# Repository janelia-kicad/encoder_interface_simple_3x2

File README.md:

- [Repository Information](#orgb147bf3)
  - [Description](#org8e3bae9)
- [Images](#org7099fdc)
- [Schematic](#org4a67db8)
- [Gerbers](#org8729698)
- [Bill of Materials](#org40f1ed6)
  - [PCB Parts](#org051be0c)
  - [Supplemental Parts](#orgbf1fa54)
  - [Vendor Parts Lists](#org75a438f)
- [Supplemental Documentation](#org5ec4243)
  - [Assembly Instructions](#org6c46454)
- [Manufacturing Archive](#org6b4d140)

# Repository Information

-   **Name:** encoder\_interface\_simple\_3x2
-   **Version:** 1.1
-   **License:** Open-Source Hardware
-   **URL:** <https://github.com/janelia-kicad/encoder_interface_simple_3x2>
-   **Author:** Peter Polidoro
-   **Email:** peter@polidoro.io

## Description

This board provides a simple encoder interace with buffered encoder signal outputs.

# Images

# Schematic

[./schematic/encoder\_interface\_simple\_3x2.pdf](./schematic/encoder_interface_simple_3x2.pdf)

# Gerbers

# Bill of Materials

## PCB Parts

| Item | Reference(s) | Quantity | Manufacturer                    | Manufacturer Part Number | Vendor   | Vendor Part Number | Description                                                       | Package            |
|---- |------------ |-------- |------------------------------- |------------------------ |-------- |------------------ |----------------------------------------------------------------- |------------------ |
| 1    | C1           | 1        | KEMET                           | C1210X104K1RAC7800       | Digi-Key | 399-13229-1-ND     | CAP CER 0.1UF 50V 10% X7R                                         | 1210 (3225 Metric) |
| 2    | MDB1         | 2        | Sullins Connector Solutions     | PBC16SAAN                | Digi-Key | S1011E-16-ND       | 16 Position Header Through Hole Male Pins                         |                    |
| 3    | P1           | 1        | Amphenol RF                     | 112661                   | Digi-Key | ACX1655-ND         | CONN BNC JACK R/A 75 OHM PCB                                      |                    |
| 4    | P2           | 1        | Molex                           | 0740991005               | Digi-Key | WM7205-ND          | CONN HEADER .100 VERT 5POS SMD                                    |                    |
| 5    | R1 R2        | 2        | Panasonic Electronic Components | ERJ-14NF3161U            | Digi-Key | P3.16KAACT-ND      | RES SMD 3.16K OHM 1% 1/2W 1210                                    |                    |
| 6    | U1           | 1        | Texas Instruments               | SN74ABT541BDWR           | Digi-Key | 296-14668-1-ND     | Buffer Non-Inverting 1 Element 8 Bit per Element Push-Pull Output | 20-SOIC            |

## Supplemental Parts

| Item | Quantity | Manufacturer            | Manufacturer Part Number | Vendor   | Vendor Part Number | Description                      |
|---- |-------- |----------------------- |------------------------ |-------- |------------------ |-------------------------------- |
| 1    | 1        | Molex                   | 0050579405               | Digi-Key | WM2903-ND          | CONN HOUSING 5POS .100 W/LATCH   |
| 2    | 5        | Molex                   | 0016021117               | Digi-Key | WM2572-ND          | CONN SOCKET 24-30AWG CRIMP GOLD  |
| 3    | 2        | TPI (Test Products Int) | 58-024-1M                | Digi-Key | 290-1010-ND        | CBL ASSY BNC PLUG-PLUG RG58 24IN |

## Vendor Parts Lists

[./bom/Digi-Key\_parts.csv](./bom/Digi-Key_parts.csv)

[./bom/supplemental\_Digi-Key\_parts.csv](./bom/supplemental_Digi-Key_parts.csv)

# Supplemental Documentation

## Assembly Instructions

-   Solder surface mount and through hole components onto the pcb.

# Manufacturing Archive

Send manufacturing zip file to your favorite PCB manufacturer for fabrication.

[./manufacturing/encoder\_interface\_simple\_3x2\_v1.1.zip](./manufacturing/encoder_interface_simple_3x2_v1.1.zip)

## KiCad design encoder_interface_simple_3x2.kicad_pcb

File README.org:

# Created 2020-10-30 Fri 10:11
#+OPTIONS: title:nil author:nil email:nil toc:t |:t ^:nil
* Repository Information

- Name :: encoder_interface_simple_3x2
- Version :: 1.1
- License :: Open-Source Hardware
- URL :: https://github.com/janelia-kicad/encoder_interface_simple_3x2
- Author :: Peter Polidoro
- Email :: peter@polidoro.io

** Description

This board provides a simple encoder interace with buffered encoder signal
outputs.

* Images

* Schematic

[[file:./schematic/encoder_interface_simple_3x2.pdf][./schematic/encoder_interface_simple_3x2.pdf]]

[[file:./schematic/images/schematic00.png]]

[[file:./schematic/images/schematic01.png]]

* Gerbers

[[file:./gerbers/images/gerbers00.png]]

[[file:./gerbers/images/gerbers01.png]]

* Bill of Materials

** PCB Parts

| Item | Reference(s) | Quantity | Manufacturer                    | Manufacturer Part Number | Vendor   | Vendor Part Number | Description                                                       | Package            |
|------+--------------+----------+---------------------------------+--------------------------+----------+--------------------+-------------------------------------------------------------------+--------------------|
|    1 | C1           |        1 | KEMET                           | C1210X104K1RAC7800       | Digi-Key | 399-13229-1-ND     | CAP CER 0.1UF 50V 10% X7R                                         | 1210 (3225 Metric) |
|    2 | MDB1         |        2 | Sullins Connector Solutions     | PBC16SAAN                | Digi-Key | S1011E-16-ND       | 16 Position Header Through Hole Male Pins                         |                    |
|    3 | P1           |        1 | Amphenol RF                     | 112661                   | Digi-Key | ACX1655-ND         | CONN BNC JACK R/A 75 OHM PCB                                      |                    |
|    4 | P2           |        1 | Molex                           | 0740991005               | Digi-Key | WM7205-ND          | CONN HEADER .100 VERT 5POS SMD                                    |                    |
|    5 | R1 R2        |        2 | Panasonic Electronic Components | ERJ-14NF3161U            | Digi-Key | P3.16KAACT-ND      | RES SMD 3.16K OHM 1% 1/2W 1210                                    |                    |
|    6 | U1           |        1 | Texas Instruments               | SN74ABT541BDWR           | Digi-Key | 296-14668-1-ND     | Buffer Non-Inverting 1 Element 8 Bit per Element Push-Pull Output | 20-SOIC            |

** Supplemental Parts

| Item | Quantity | Manufacturer            | Manufacturer Part Number | Vendor   | Vendor Part Number | Description                      |
|------+----------+-------------------------+--------------------------+----------+--------------------+----------------------------------|
|    1 |        1 | Molex                   |               0050579405 | Digi-Key | WM2903-ND          | CONN HOUSING 5POS .100 W/LATCH   |
|    2 |        5 | Molex                   |               0016021117 | Digi-Key | WM2572-ND          | CONN SOCKET 24-30AWG CRIMP GOLD  |
|    3 |        2 | TPI (Test Products Int) |                58-024-1M | Digi-Key | 290-1010-ND        | CBL ASSY BNC PLUG-PLUG RG58 24IN |
#+TBLFM: $1=@#-1

** Vendor Parts Lists

[[file:./bom/Digi-Key_parts.csv][./bom/Digi-Key_parts.csv]]

[[file:./bom/supplemental_Digi-Key_parts.csv][./bom/supplemental_Digi-Key_parts.csv]]

* Supplemental Documentation

** Assembly Instructions

- Solder surface mount and through hole components onto the pcb.

* Manufacturing Archive

Send manufacturing zip file to your favorite PCB manufacturer for fabrication.

[[file:./manufacturing/encoder_interface_simple_3x2_v1.1.zip][./manufacturing/encoder_interface_simple_3x2_v1.1.zip]]

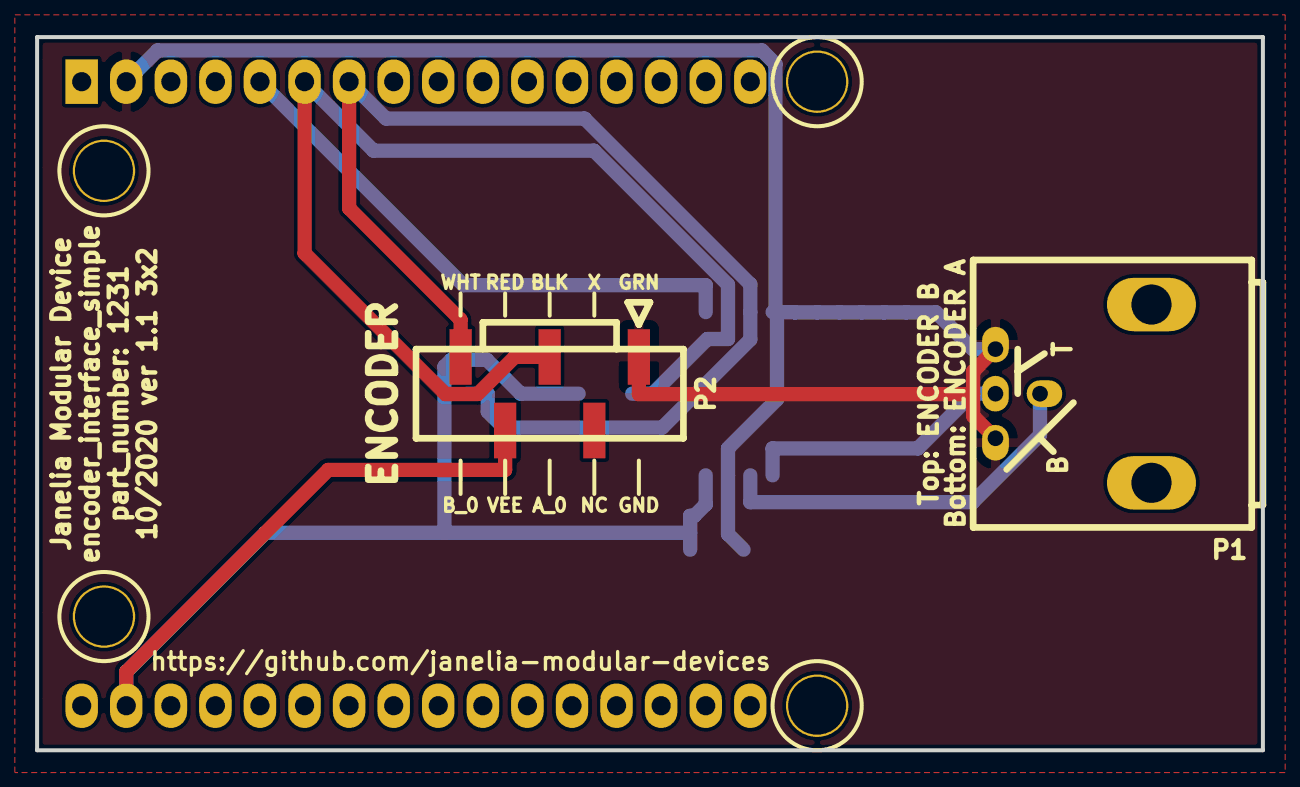
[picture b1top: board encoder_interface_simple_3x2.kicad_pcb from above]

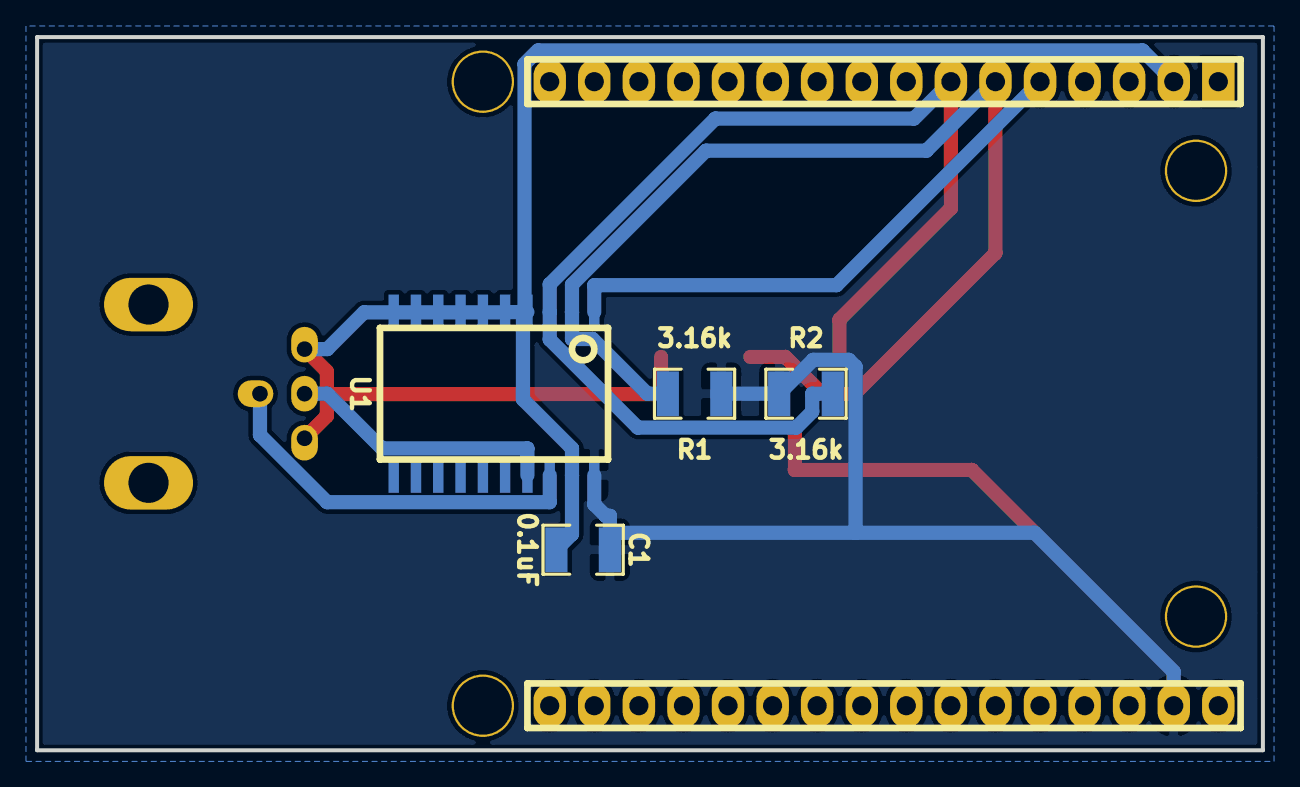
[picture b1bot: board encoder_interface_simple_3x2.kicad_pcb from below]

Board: 2 copper layers, 69.8 x 40.6 mm, 7 parts (4 on the bottom side), 7 nets.

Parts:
C1: 0.1uF; SM1210
MDB1: VAL**; MODULAR_DEVICE_BASE_3X2_MALE
P1: BNC_DOUBLE_RA; BNC_DOUBLE
P2: HEADER_01X05_SMD_SHR; Header_Shrouded_5_Pin_SMD
R1, R2: 3.16k; SM1210
U1: SN74ABT541BDWR; SOIC_20

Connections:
/ENCODER_A: MDB1.3, P2.3, R1.2, U1.2
/ENCODER_A_BUF: P1.1, U1.18
/ENCODER_B: MDB1.4, P2.5, R2.2, U1.3
/ENCODER_B_BUF: P1.3, U1.17
/~ENABLE: MDB1.2, U1.1
GND: C1.2, MDB1.GND, P1.2, P1.4, P2.1, U1.4, U1.5, U1.6, U1.7, U1.8, U1.9, U1.10, U1.19
VEE: C1.1, MDB1.VEE, P2.4, R1.1, R2.1, U1.20

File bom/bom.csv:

Item,Reference(s),Quantity,Manufacturer,Manufacturer Part Number,Vendor,Vendor Part Number,Description,Package
1,C1,1,KEMET,C1210X104K1RAC7800,Digi-Key,399-13229-1-ND,CAP CER 0.1UF 50V 10% X7R,1210 (3225 Metric)
2,MDB1,2,Sullins Connector Solutions,PBC16SAAN,Digi-Key,S1011E-16-ND,16 Position Header Through Hole Male Pins,
3,P1,1,Amphenol RF,112661,Digi-Key,ACX1655-ND,CONN BNC JACK R/A 75 OHM PCB,
4,P2,1,Molex,0740991005,Digi-Key,WM7205-ND,CONN HEADER .100 VERT 5POS SMD,
5,R1 R2,2,Panasonic Electronic Components,ERJ-14NF3161U,Digi-Key,P3.16KAACT-ND,RES SMD 3.16K OHM 1% 1/2W 1210,
6,U1,1,Texas Instruments,SN74ABT541BDWR,Digi-Key,296-14668-1-ND,Buffer Non-Inverting 1 Element 8 Bit per Element Push-Pull Output,20-SOIC

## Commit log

2017-03-09 Initial commit.
2017-03-09 First pass at schematic.
2017-03-10 Finished version 1.0.
2017-03-10 Added parts to digikey order.
2017-03-24 Updated documentation.
2017-06-15 Removed .cmp file.
2017-09-13 Updated 0.1uF capacitors.
2017-09-22 Removed extra libraries.
2018-01-08 Updated to v4.
2018-01-08 Added v4 files.
2018-01-08 Updated gitignore.
2018-03-09 Update license from software to hardware.
2018-04-12 README.md -> README.org.
2018-04-19 Added .DS_Store to .gitignore.
2018-05-16 Added generate_kicad_documentation submodule.
2018-05-17 Updated submodules.
2018-08-12 Marked extra Teensy pins.
2018-08-12 Removed v4 files.
2018-08-24 Removed F.SilkS from pads.
2020-10-29 Output buffered encoder signals only
2020-10-29 Update documentation
2020-10-30 Remove extraneous gerber files
2021-09-16 Update email address
2021-09-21 Remove ignored files
2022-02-22 Add guix files
2022-02-23 Add guix documentation
